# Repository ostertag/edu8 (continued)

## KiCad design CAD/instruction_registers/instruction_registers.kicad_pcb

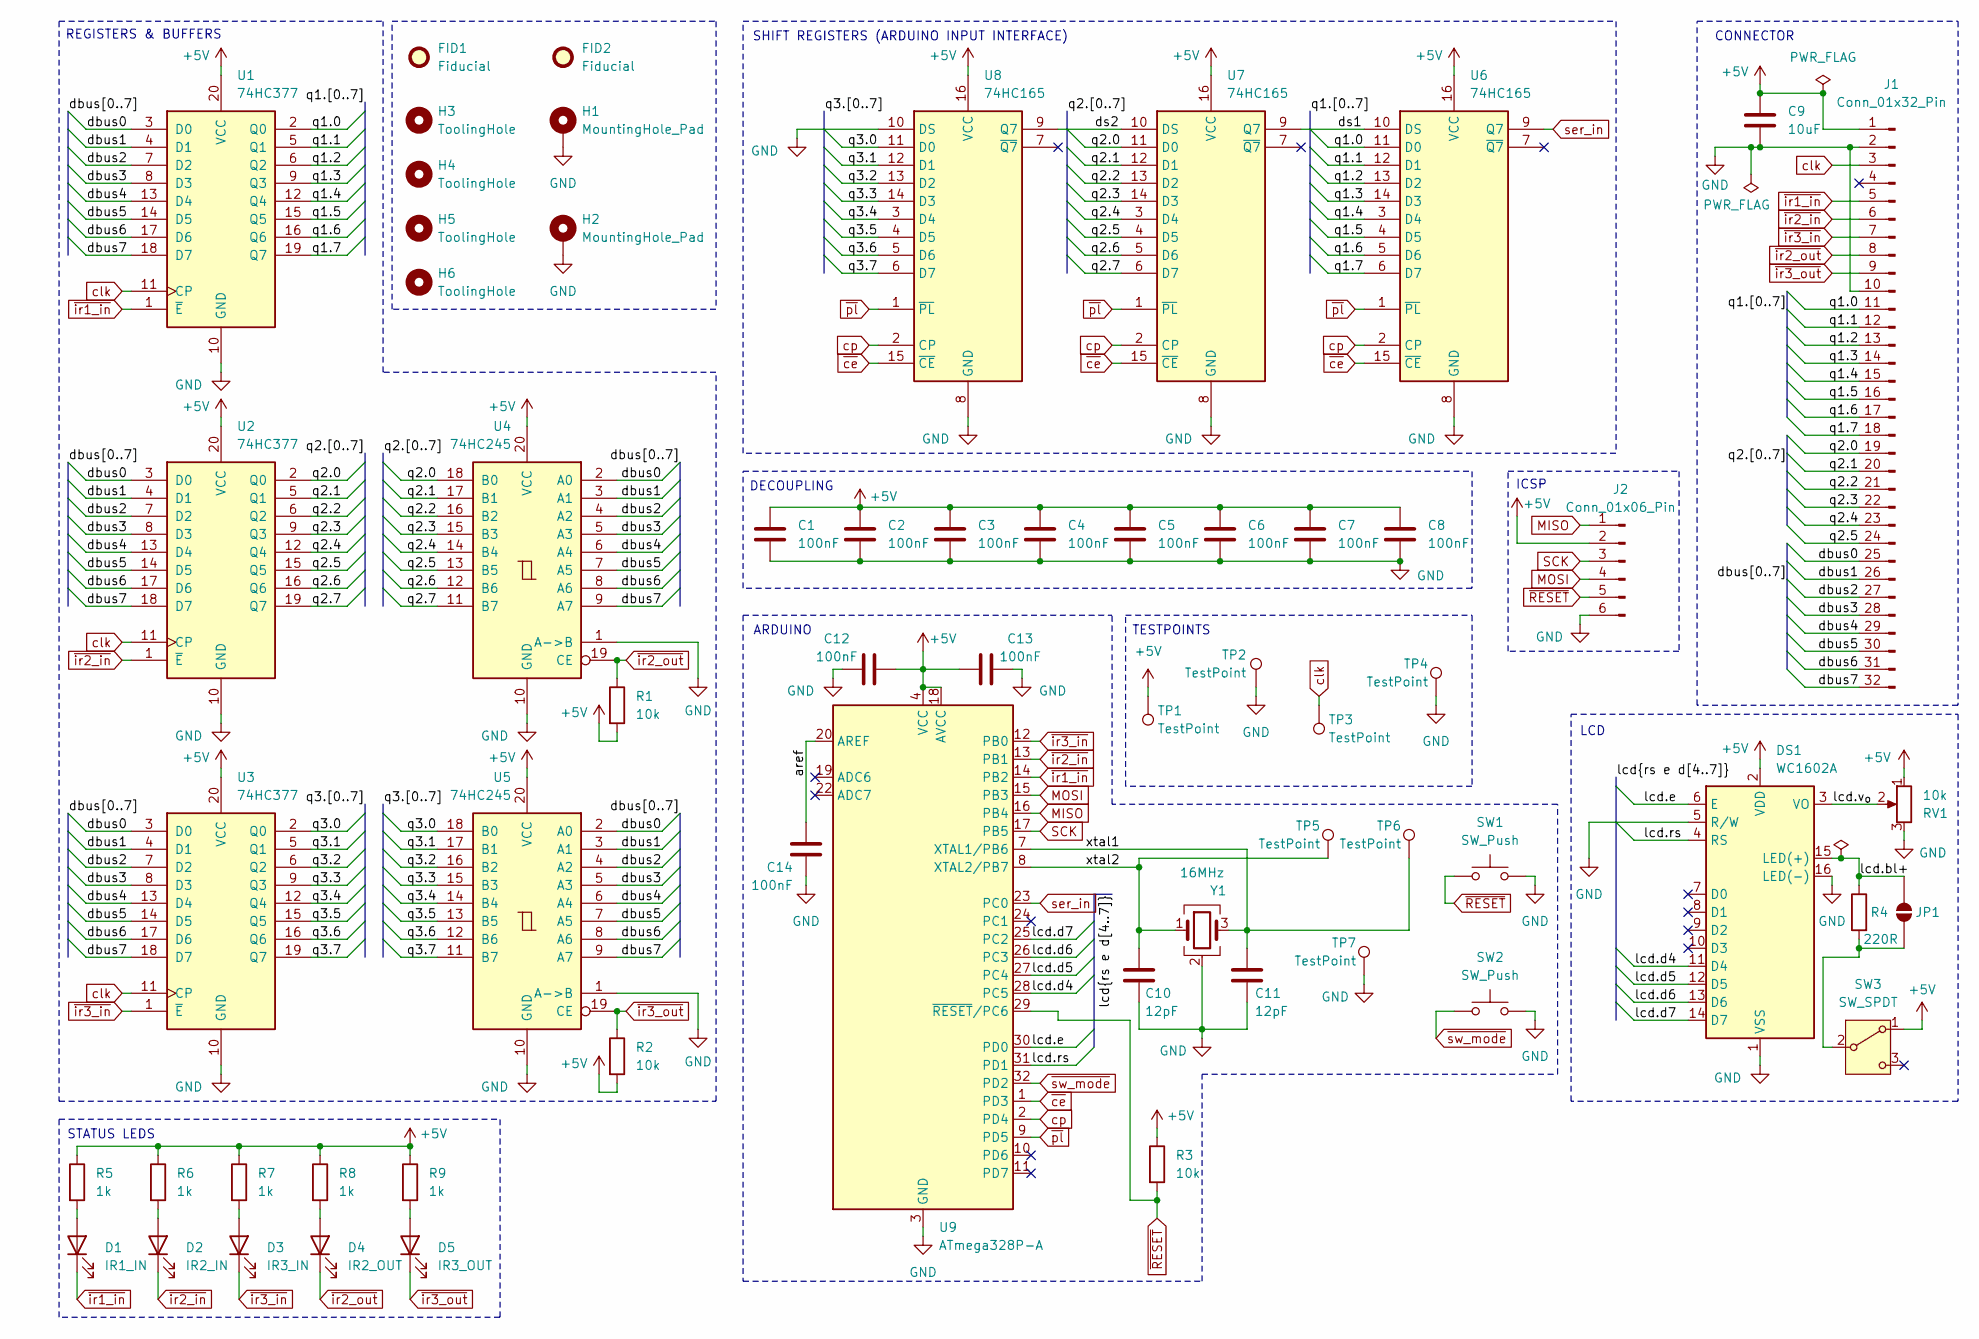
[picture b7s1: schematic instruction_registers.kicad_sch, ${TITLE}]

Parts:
C1, C2, C3, C4, C5, C6, C7, C8, C12, C13, C14: 100nF; C_0805_2012Metric; LCSC C28233
C9: 10uF; C_0805_2012Metric; LCSC C15850
C10, C11: 12pF; C_0805_2012Metric; LCSC C1792
D1: IR1_IN; LED_0805_2012Metric; LCSC C2297
D2: IR2_IN; LED_0805_2012Metric; LCSC C2297
D3: IR3_IN; LED_0805_2012Metric; LCSC C2297
D4: IR2_OUT; LED_0805_2012Metric; LCSC C2296
D5: IR3_OUT; LED_0805_2012Metric; LCSC C2296
DS1: WC1602A
FID1, FID2: Fiducial; Fiducial_0.5mm_Mask1mm
H1, H2: MountingHole_Pad; MountingHole_2.5mm_Pad_Via
H3, H4, H5, H6: ToolingHole; ToolingHole_1.152mm
J1: Conn_01x32_Pin; PinHeader_2x16_P2.54mm_Horizontal; LCSC C18905914
J2: Conn_01x06_Pin; PinHeader_2x03_P2.54mm_Vertical
JP1: SolderJumper_2_Open; SolderJumper-2_P1.3mm_Open_RoundedPad1.0x1.5mm
R1, R2, R3: 10k; R_0805_2012Metric; LCSC C17414
R4: 220R; R_0805_2012Metric; LCSC C17557
R5, R6, R7, R8, R9: 1k; R_0805_2012Metric; LCSC C17513
RV1: 10k; Potentiometer_Bourns_3314J_Vertical; LCSC C36376
SW1, SW2: SW_Push; SW_Push_1P1T_XKB_TS-1187A; LCSC C318884
SW3: SW_SPDT; SW_SPDT_PCM12; LCSC C221841
TP1, TP2, TP3, TP4, TP5, TP6, TP7: TestPoint; TestPoint_THTPad_D1.0mm_Drill0.5mm
U1, U2, U3: 74HC377; SO-20_5.3x12.6mm_P1.27mm; LCSC C7647
U4, U5: 74HC245; SOIC-20W_7.5x12.8mm_P1.27mm; LCSC C5625
U6, U7, U8: 74HC165; SO-16_3.9x9.9mm_P1.27mm; LCSC C5613
U9: ATmega328P-A; TQFP-32_7x7mm_P0.8mm; LCSC C14877
Y1: 16MHz; Crystal_SMD_3225-4Pin_3.2x2.5mm; LCSC C13738

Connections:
+5V: C1.1, C2.1, C3.1, C4.1, C5.1, C6.1, C7.1, C8.1, C9.1, C12.2, C13.1, DS1.2 (VDD), J1.1, J2.2, R1.2, R2.2, R3.1, R5.1, R6.1, R7.1, R8.1, R9.1, RV1.1, SW3.1 (A), TP1.1 (1_1), U1.20 (VCC), U2.20 (VCC), U3.20 (VCC), U4.20 (VCC), U5.20 (VCC), U6.16 (VCC), U7.16 (VCC), U8.16 (VCC), U9.4 (VCC), U9.6 (VCC), U9.18 (AVCC)
/aref: C14.1, U9.20 (AREF)
/dbus0: J1.25, U1.3 (D0), U2.3 (D0), U3.3 (D0), U4.2 (A0), U5.2 (A0)
/dbus1: J1.26, U1.4 (D1), U2.4 (D1), U3.4 (D1), U4.3 (A1), U5.3 (A1)
/dbus2: J1.27, U1.7 (D2), U2.7 (D2), U3.7 (D2), U4.4 (A2), U5.4 (A2)
/dbus3: J1.28, U1.8 (D3), U2.8 (D3), U3.8 (D3), U4.5 (A3), U5.5 (A3)
/dbus4: J1.29, U1.13 (D4), U2.13 (D4), U3.13 (D4), U4.6 (A4), U5.6 (A4)
/dbus5: J1.30, U1.14 (D5), U2.14 (D5), U3.14 (D5), U4.7 (A5), U5.7 (A5)
/dbus6: J1.31, U1.17 (D6), U2.17 (D6), U3.17 (D6), U4.8 (A6), U5.8 (A6)
/dbus7: J1.32, U1.18 (D7), U2.18 (D7), U3.18 (D7), U4.9 (A7), U5.9 (A7)
/ds1: U6.10 (DS), U7.9 (Q7)
/ds2: U7.10 (DS), U8.9 (Q7)
/lcd.bl+: DS1.15 (LED(+)), JP1.2 (B), R4.1
/lcd.d4: DS1.11 (D4), U9.28 (PC5)
/lcd.d5: DS1.12 (D5), U9.27 (PC4)
/lcd.d6: DS1.13 (D6), U9.26 (PC3)
/lcd.d7: DS1.14 (D7), U9.25 (PC2)
/lcd.e: DS1.6 (E), U9.30 (PD0)
/lcd.rs: DS1.4 (RS), U9.31 (PD1)
/lcd.v_{o}: DS1.3 (VO), RV1.2
/q1.0: J1.11, U1.2 (Q0), U6.11 (D0)
/q1.1: J1.12, U1.5 (Q1), U6.12 (D1)
/q1.2: J1.13, U1.6 (Q2), U6.13 (D2)
/q1.3: J1.14, U1.9 (Q3), U6.14 (D3)
/q1.4: J1.15, U1.12 (Q4), U6.3 (D4)
/q1.5: J1.16, U1.15 (Q5), U6.4 (D5)
/q1.6: J1.17, U1.16 (Q6), U6.5 (D6)
/q1.7: J1.18, U1.19 (Q7), U6.6 (D7)
/q2.0: J1.19, U2.2 (Q0), U4.18 (B0), U7.11 (D0)
/q2.1: J1.20, U2.5 (Q1), U4.17 (B1), U7.12 (D1)
/q2.2: J1.21, U2.6 (Q2), U4.16 (B2), U7.13 (D2)
/q2.3: J1.22, U2.9 (Q3), U4.15 (B3), U7.14 (D3)
/q2.4: J1.23, U2.12 (Q4), U4.14 (B4), U7.3 (D4)
/q2.5: J1.24, U2.15 (Q5), U4.13 (B5), U7.4 (D5)
/q2.6: U2.16 (Q6), U4.12 (B6), U7.5 (D6)
/q2.7: U2.19 (Q7), U4.11 (B7), U7.6 (D7)
/q3.0: U3.2 (Q0), U5.18 (B0), U8.11 (D0)
/q3.1: U3.5 (Q1), U5.17 (B1), U8.12 (D1)
/q3.2: U3.6 (Q2), U5.16 (B2), U8.13 (D2)
/q3.3: U3.9 (Q3), U5.15 (B3), U8.14 (D3)
/q3.4: U3.12 (Q4), U5.14 (B4), U8.3 (D4)
/q3.5: U3.15 (Q5), U5.13 (B5), U8.4 (D5)
/q3.6: U3.16 (Q6), U5.12 (B6), U8.5 (D6)
/q3.7: U3.19 (Q7), U5.11 (B7), U8.6 (D7)
/xtal1: C11.1, TP6.1 (1_1), U9.7 (XTAL1/PB6), Y1.3
/xtal2: C10.1, TP5.1 (1_1), U9.8 (XTAL2/PB7), Y1.1
GND: C1.2, C2.2, C3.2, C4.2, C5.2, C6.2, C7.2, C8.2, C9.2, C10.2, C11.2, C12.1, C13.2, C14.2, DS1.1 (VSS), DS1.5 (R/W), DS1.16 (LED(-)), H1.1 (1_1), H2.1 (1_1), J1.2, J1.10, J2.6, RV1.3, SW1.2, SW2.2, TP2.1 (1_1), TP4.1 (1_1), TP7.1 (1_1), U1.10 (GND), U2.10 (GND), U3.10 (GND), U4.1 (A->B), U4.10 (GND), U5.1 (A->B), U5.10 (GND), U6.8 (GND), U7.8 (GND), U8.8 (GND), U8.10 (DS), U9.3 (GND), U9.5 (GND), U9.21 (GND), Y1.2 (G), Y1.4 (G)
MISO: J2.1, U9.16 (PB4)
MOSI: J2.4, U9.15 (PB3)
unnamed: D1.2 (A), R5.2
unnamed: D2.2 (A), R6.2
unnamed: D3.2 (A), R7.2
unnamed: D4.2 (A), R8.2
unnamed: D5.2 (A), R9.2
unnamed: JP1.1 (A), R4.2, SW3.2 (B)
SCK: J2.3, U9.17 (PB5)
clk: J1.3, TP3.1 (1_1), U1.11 (CP), U2.11 (CP), U3.11 (CP)
cp: U6.2 (CP), U7.2 (CP), U8.2 (CP), U9.2 (PD4)
ser_in: U6.9 (Q7), U9.23 (PC0)
~RESET: J2.5, R3.2, SW1.1, U9.29 (~RESET/PC6)
~ce: U6.15 (~CE), U7.15 (~CE), U8.15 (~CE), U9.1 (PD3)
~ir1_in: D1.1 (K), J1.5, U1.1 (~E), U9.14 (PB2)
~ir2_in: D2.1 (K), J1.6, U2.1 (~E), U9.13 (PB1)
~ir2_out: D4.1 (K), J1.8, R1.1, U4.19 (CE)
~ir3_in: D3.1 (K), J1.7, U3.1 (~E), U9.12 (PB0)
~ir3_out: D5.1 (K), J1.9, R2.1, U5.19 (CE)
~pl: U6.1 (~PL), U7.1 (~PL), U8.1 (~PL), U9.9 (PD5)
~sw_mode: SW2.1, U9.32 (PD2)

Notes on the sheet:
ARDUINO
TESTPOINTS
CONNECTOR
STATUS LEDS
DECOUPLING
LCD
ICSP
REGISTERS & BUFFERS
SHIFT REGISTERS (ARDUINO INPUT INTERFACE)

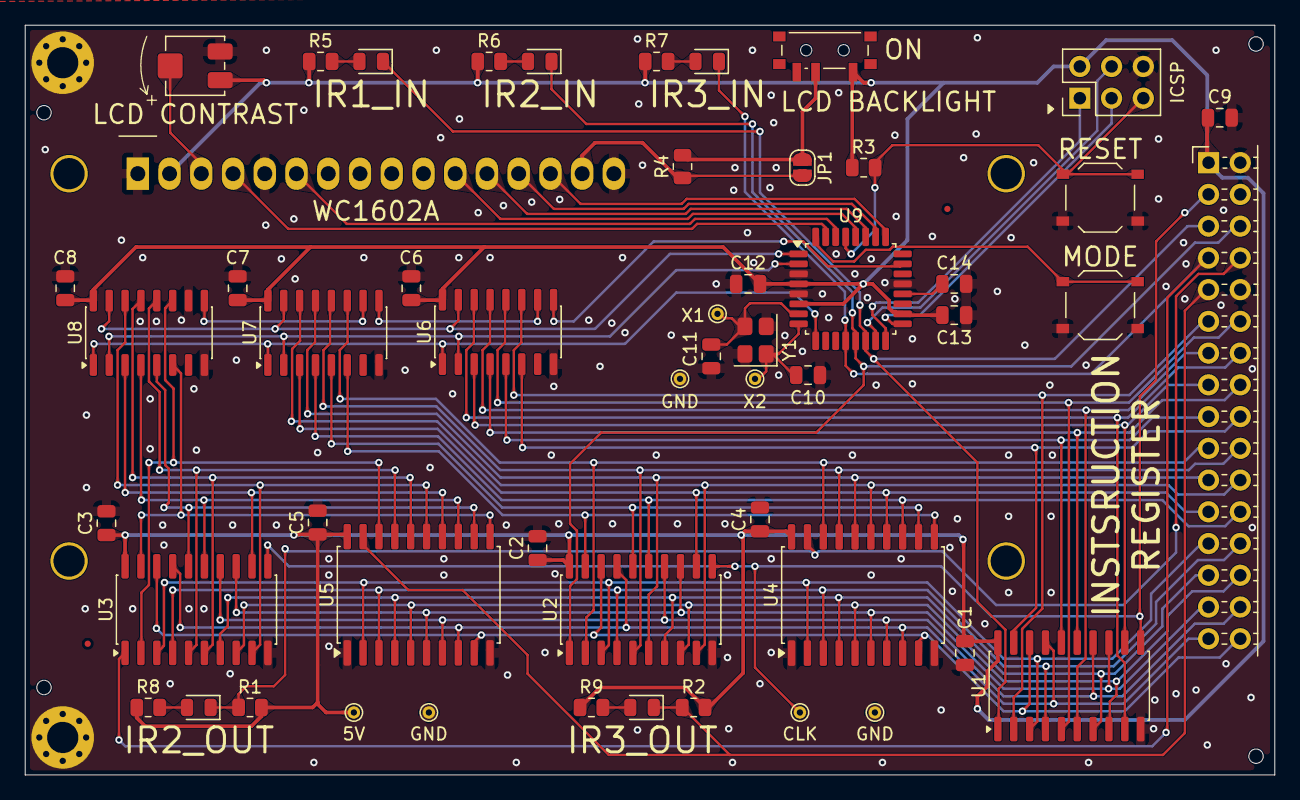
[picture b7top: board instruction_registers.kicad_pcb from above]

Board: 2 copper layers, 100.0 x 60.0 mm, 62 parts (1 on the bottom side), 68 nets.

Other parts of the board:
Ref**: Val**; by-nc-sa.eu

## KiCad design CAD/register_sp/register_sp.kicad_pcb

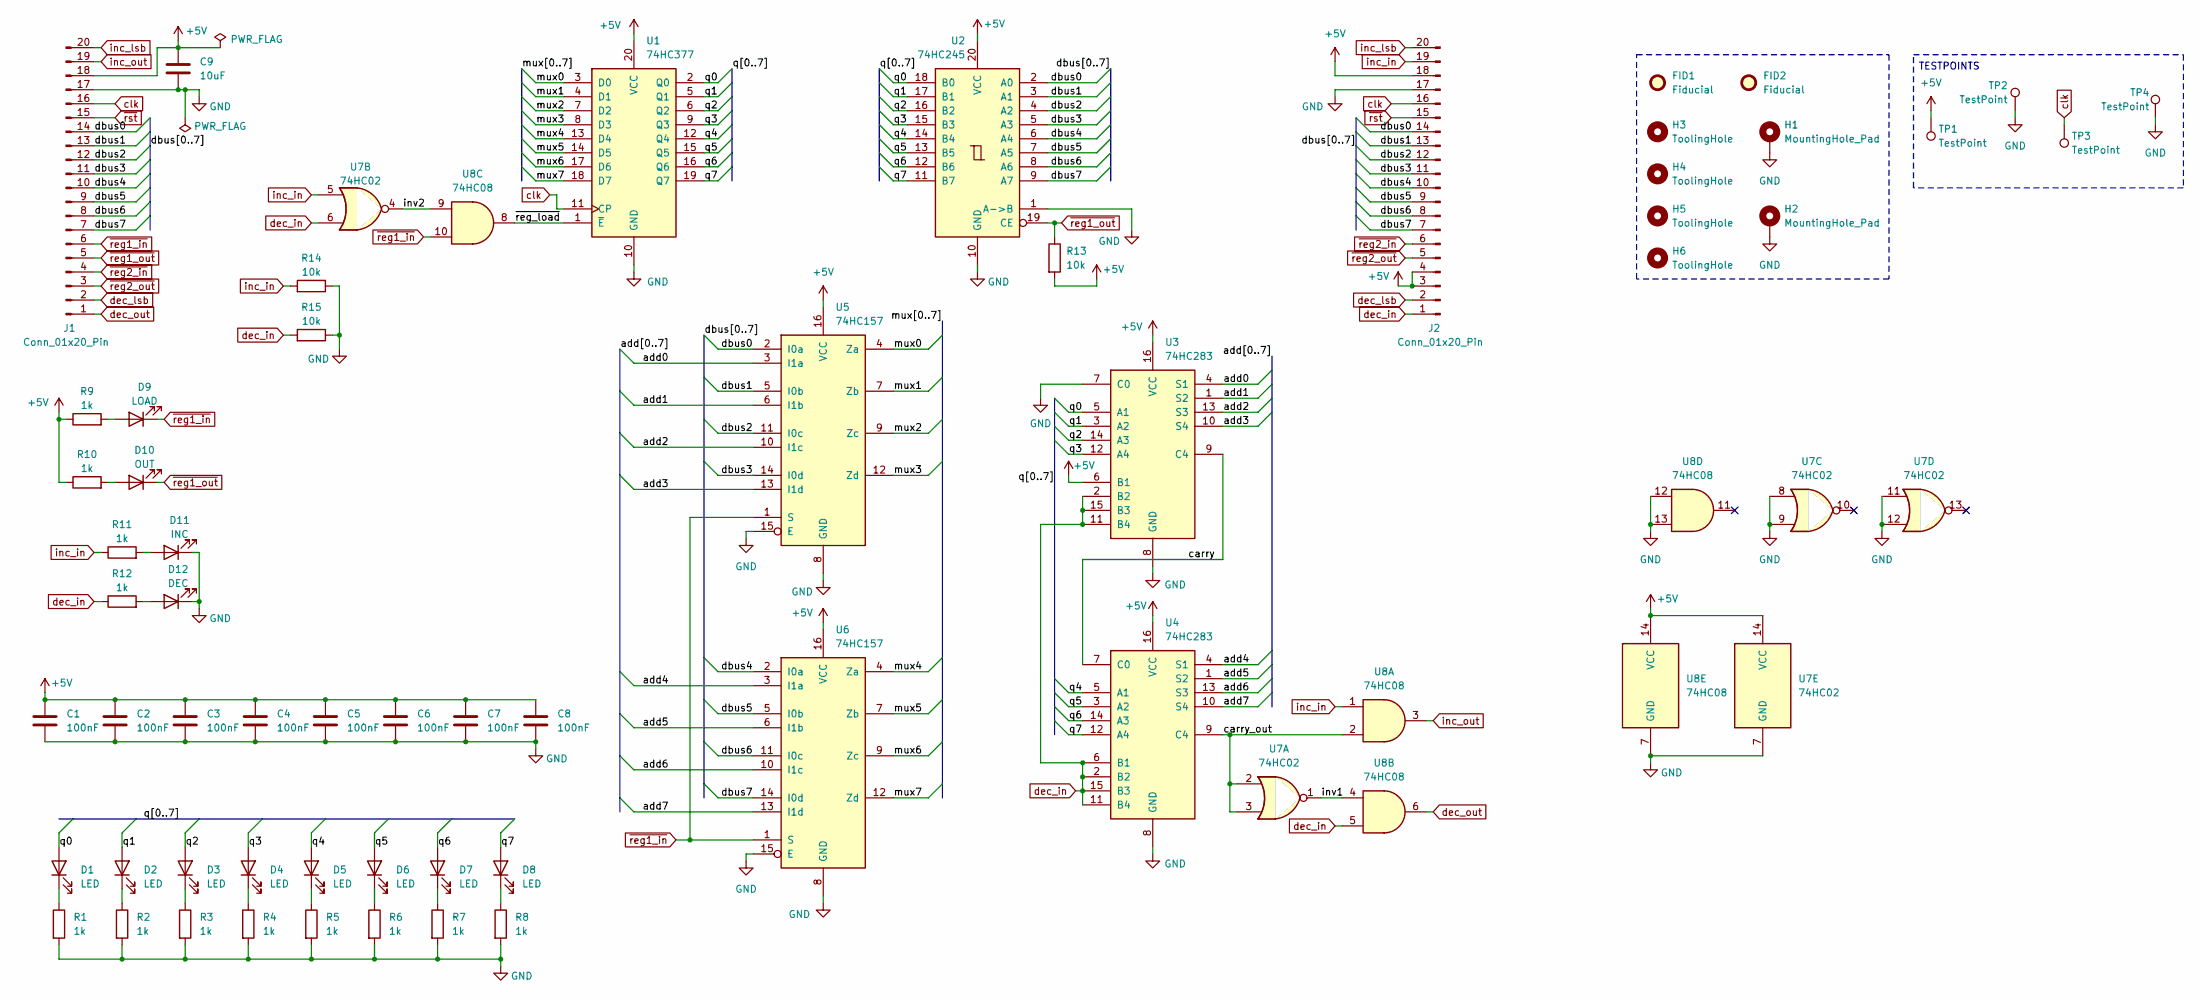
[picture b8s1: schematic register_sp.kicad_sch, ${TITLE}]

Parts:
C1, C2, C3, C4, C5, C6, C7, C8: 100nF; C_0805_2012Metric; LCSC C28233
C9: 10uF; C_0805_2012Metric; LCSC C15850
D1, D2, D3, D4, D5, D6, D7, D8: LED; LED_0805_2012Metric; LCSC C84256
D9: LOAD; LED_0805_2012Metric; LCSC C2297
D10: OUT; LED_0805_2012Metric; LCSC C2296
D11: INC; LED_0805_2012Metric
D12: DEC; LED_0805_2012Metric
FID1, FID2: Fiducial; Fiducial_0.5mm_Mask1mm
H1, H2: MountingHole_Pad; MountingHole_2.5mm_Pad_Via
H3, H4, H5, H6: ToolingHole; ToolingHole_1.152mm
J1: Conn_01x20_Pin; PinHeader_2x10_P2.54mm_Horizontal; LCSC C18905907
J2: Conn_01x20_Pin; PinSocket_2x10_P2.54mm_Horizontal; LCSC C2897429
R1, R2, R3, R4, R5, R6, R7, R8, R9, R10, R11, R12: 1k; R_0805_2012Metric; LCSC C17513
R13, R14, R15: 10k; R_0805_2012Metric; LCSC C17414
TP1, TP2, TP3, TP4: TestPoint; TestPoint_THTPad_D1.0mm_Drill0.5mm
U1: 74HC377; SO-20_5.3x12.6mm_P1.27mm; LCSC C7647
U2: 74HC245; SOIC-20W_7.5x12.8mm_P1.27mm; LCSC C5625
U3, U4: 74HC283; SO-16_3.9x9.9mm_P1.27mm; LCSC C24833609
U5, U6: 74HC157; SO-16_3.9x9.9mm_P1.27mm; LCSC C6823
U7: 74HC02; SO-14_3.9x8.65mm_P1.27mm; LCSC C350559
U8: 74HC08; SO-14_3.9x8.65mm_P1.27mm; LCSC C5593

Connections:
+5V: C1.1, C2.1, C3.1, C4.1, C5.1, C6.1, C7.1, C8.1, C9.1, J1.18, J2.3, J2.4, J2.18, R9.1, R10.1, R13.2, TP1.1 (1_1), U1.20 (VCC), U2.20 (VCC), U3.6 (B1), U3.16 (VCC), U4.16 (VCC), U5.16 (VCC), U6.16 (VCC), U7.14 (VCC), U8.14 (VCC)
/add0: U3.4 (S1), U5.3 (I1a)
/add1: U3.1 (S2), U5.6 (I1b)
/add2: U3.13 (S3), U5.10 (I1c)
/add3: U3.10 (S4), U5.13 (I1d)
/add4: U4.4 (S1), U6.3 (I1a)
/add5: U4.1 (S2), U6.6 (I1b)
/add6: U4.13 (S3), U6.10 (I1c)
/add7: U4.10 (S4), U6.13 (I1d)
/carry: U3.9 (C4), U4.7 (C0)
/carry_out: U4.9 (C4), U7.2, U7.3, U8.2
/dbus0: J1.14, J2.14, U2.2 (A0), U5.2 (I0a)
/dbus1: J1.13, J2.13, U2.3 (A1), U5.5 (I0b)
/dbus2: J1.12, J2.12, U2.4 (A2), U5.11 (I0c)
/dbus3: J1.11, J2.11, U2.5 (A3), U5.14 (I0d)
/dbus4: J1.10, J2.10, U2.6 (A4), U6.2 (I0a)
/dbus5: J1.9, J2.9, U2.7 (A5), U6.5 (I0b)
/dbus6: J1.8, J2.8, U2.8 (A6), U6.11 (I0c)
/dbus7: J1.7, J2.7, U2.9 (A7), U6.14 (I0d)
/inv1: U7.1, U8.4
/inv2: U7.4, U8.9
/mux0: U1.3 (D0), U5.4 (Za)
/mux1: U1.4 (D1), U5.7 (Zb)
/mux2: U1.7 (D2), U5.9 (Zc)
/mux3: U1.8 (D3), U5.12 (Zd)
/mux4: U1.13 (D4), U6.4 (Za)
/mux5: U1.14 (D5), U6.7 (Zb)
/mux6: U1.17 (D6), U6.9 (Zc)
/mux7: U1.18 (D7), U6.12 (Zd)
/q0: D1.2 (A), U1.2 (Q0), U2.18 (B0), U3.5 (A1)
/q1: D2.2 (A), U1.5 (Q1), U2.17 (B1), U3.3 (A2)
/q2: D3.2 (A), U1.6 (Q2), U2.16 (B2), U3.14 (A3)
/q3: D4.2 (A), U1.9 (Q3), U2.15 (B3), U3.12 (A4)
/q4: D5.2 (A), U1.12 (Q4), U2.14 (B4), U4.5 (A1)
/q5: D6.2 (A), U1.15 (Q5), U2.13 (B5), U4.3 (A2)
/q6: D7.2 (A), U1.16 (Q6), U2.12 (B6), U4.14 (A3)
/q7: D8.2 (A), U1.19 (Q7), U2.11 (B7), U4.12 (A4)
/~reg_load: U1.1 (~E), U8.8
GND: C1.2, C2.2, C3.2, C4.2, C5.2, C6.2, C7.2, C8.2, C9.2, D11.1 (K), D12.1 (K), H1.1 (1_1), H2.1 (1_1), J1.17, J2.17, R1.2, R2.2, R3.2, R4.2, R5.2, R6.2, R7.2, R8.2, R14.1, R15.1, TP2.1 (1_1), TP4.1 (1_1), U1.10 (GND), U2.1 (A->B), U2.10 (GND), U3.7 (C0), U3.8 (GND), U4.8 (GND), U5.8 (GND), U5.15 (E), U6.8 (GND), U6.15 (E), U7.7 (GND), U7.8, U7.9, U7.11, U7.12, U8.7 (GND), U8.12, U8.13
unnamed: D1.1 (K), R1.1
unnamed: D2.1 (K), R2.1
unnamed: D3.1 (K), R3.1
unnamed: D4.1 (K), R4.1
unnamed: D5.1 (K), R5.1
unnamed: D6.1 (K), R6.1
unnamed: D7.1 (K), R7.1
unnamed: D8.1 (K), R8.1
unnamed: D9.2 (A), R9.2
unnamed: D10.2 (A), R10.2
unnamed: D11.2 (A), R11.2
unnamed: D12.2 (A), R12.2
clk: J1.16, J2.16, TP3.1 (1_1), U1.11 (CP)
dec_in: J2.1, R12.1, R15.2, U3.2 (B2), U3.11 (B4), U3.15 (B3), U4.2 (B2), U4.6 (B1), U4.11 (B4), U4.15 (B3), U7.6, U8.5
dec_lsb: J1.2, J2.2
dec_out: J1.1, U8.6
inc_in: J2.19, R11.1, R14.2, U7.5, U8.1
inc_lsb: J1.20, J2.20
inc_out: J1.19, U8.3
~reg1_in: D9.1 (K), J1.6, U5.1 (S), U6.1 (S), U8.10
~reg1_out: D10.1 (K), J1.5, R13.1, U2.19 (CE)
~reg2_in: J1.4, J2.6
~reg2_out: J1.3, J2.5
~rst: J1.15, J2.15

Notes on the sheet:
TESTPOINTS

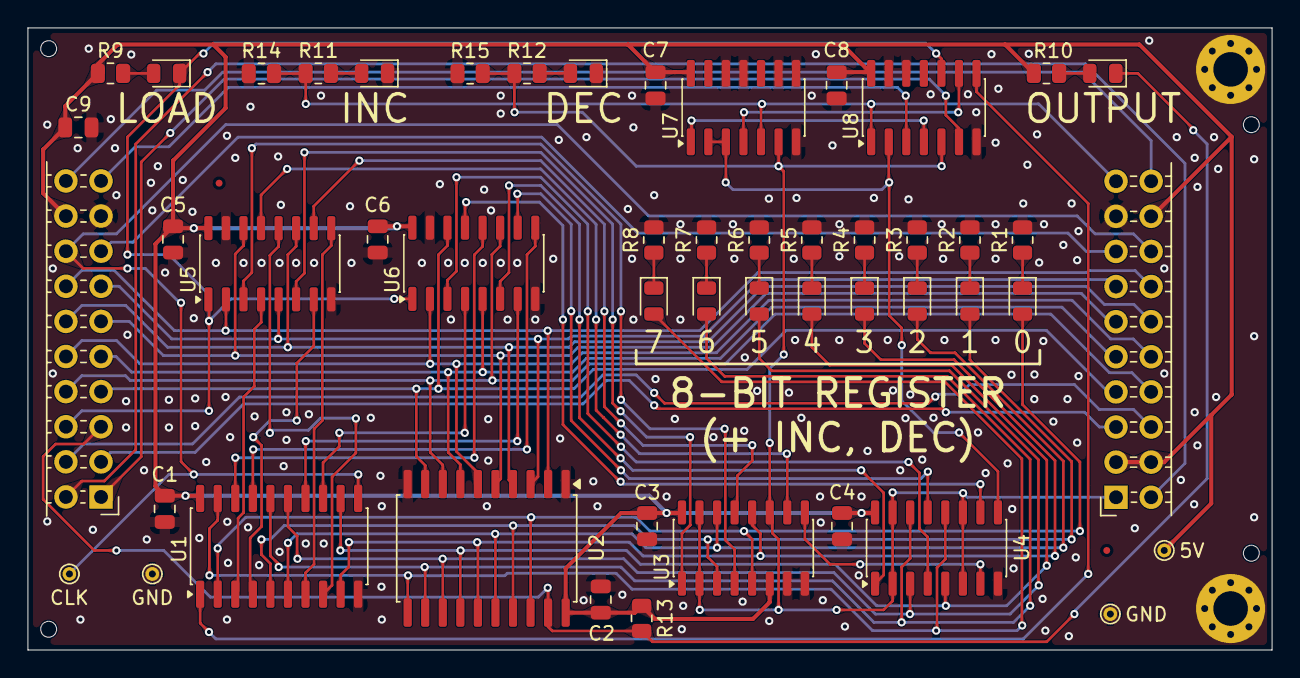
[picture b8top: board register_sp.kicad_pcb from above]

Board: 2 copper layers, 90.0 x 45.0 mm, 59 parts (1 on the bottom side), 63 nets.

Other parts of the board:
Ref**: Val**; by-nc-sa.eu

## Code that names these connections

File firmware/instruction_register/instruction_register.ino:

#include <LiquidCrystal.h>

// shift registers
const int CP_PIN = 4;
const int DATA_IN_PIN = 14;
const int CE_PIN = 3;
const int PL_PIN = 5;

// control signals
const int IR1_IN_PIN = 10;
const int IR2_IN_PIN = 9;
const int IR3_IN_PIN = 8;

// button
const int SW_MODE_PIN = 2;

// lcd
const int RS_PIN = 1;
const int E_PIN = 0;
const int D4_PIN = 19;
const int D5_PIN = 18;
const int D6_PIN = 17;
const int D7_PIN = 16;

LiquidCrystal lcd(RS_PIN, E_PIN, D4_PIN, D5_PIN, D6_PIN, D7_PIN);

bool ir1_in_state, ir2_in_state, ir3_in_state;

void loadWord() {
    digitalWrite(PL_PIN, LOW);
    delay(1);
    digitalWrite(PL_PIN, HIGH);
    delay(1);
}

uint8_t readByte() {
    uint8_t val = 0;
    for (int i = 7; i >= 0; i--) {
        val |= (digitalRead(DATA_IN_PIN) << i);
        digitalWrite(CP_PIN, HIGH);
        delay(1);
        digitalWrite(CP_PIN, LOW);
        delay(1);
    }
    return val;
}

void setup() {

  // shift registers
  pinMode(CP_PIN, OUTPUT);
  digitalWrite(CP_PIN, LOW);
  pinMode(CE_PIN, OUTPUT);
  digitalWrite(CE_PIN, LOW);
  pinMode(PL_PIN, OUTPUT);
  digitalWrite(PL_PIN, HIGH);
  pinMode(DATA_IN_PIN, INPUT);

  // control signals
  pinMode(IR1_IN_PIN, INPUT);
  pinMode(IR2_IN_PIN, INPUT);
  pinMode(IR3_IN_PIN, INPUT);
  
  // button TMP
  pinMode(SW_MODE_PIN, INPUT_PULLUP);

  // lcd
  lcd.begin(16, 2);
  lcd.clear();

  ir1_in_state = false;
  ir2_in_state = false;
  ir3_in_state = false;
  
}

char hexChar(uint8_t nibble) {
  if (nibble <= 9) return '0' + nibble;
  return 'A' + nibble - 10;
}

void updateDisplay() {
  loadWord();
  uint8_t q1 = readByte();
  uint8_t q2 = readByte();
  uint8_t q3 = readByte();
  lcd.clear();
  lcd.print(hexChar((q1 >> 4) & 0x0f));
  lcd.print(hexChar(q1 & 0x0f));
  lcd.print("  ");
  lcd.print(hexChar((q2 >> 4) & 0x0f));
  lcd.print(hexChar(q2 & 0x0f));
  lcd.print("  ");
  lcd.print(hexChar((q3 >> 4) & 0x0f));
  lcd.print(hexChar(q3 & 0x0f));
}

void loop() {
  // bool change = false;
  // if (digitalRead(IR1_IN_PIN) != ir1_in_state) {
  //   ir1_in_state = !ir1_in_state;
  //   change = true;
  // }
  // if (digitalRead(IR2_IN_PIN) != ir2_in_state) {
  //   ir2_in_state = !ir2_in_state;
  //   change = true;
  // }
  // if (digitalRead(IR3_IN_PIN) != ir3_in_state) {
  //   ir3_in_state = !ir3_in_state;
  //   change = true;
  // }

  // if (change) {
  //   updateDisplay();
  // }

  // delay(10);

  static int counter = 0;
  lcd.clear();
  lcd.print("Hello, World!");
  lcd.setCursor(0, 1);
  lcd.print("counter: ");
  lcd.print(counter++);
  delay(2000);
}

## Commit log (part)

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2026-02-26 Add vias, GND planes, QR code, version and other details
2026-02-26 Other changes
2026-03-01 setup directories
2026-03-01 add general register
2026-03-01 add NetClasses, TestPads, remove jumper pins
2026-03-03 fix HC245 dir signal
2026-03-03 add components to library
2026-03-03 add text variables for revision, etc.
2026-03-03 fix variables
2026-03-03 add Motherboard, schematic not finished
2026-03-03 add Status Word schematic
2026-03-04 add Status Word PCB, not finished
2026-03-09 add mounting holes, pull-up, test points in SW
2026-03-10 update silkscreen qr code, license, add images
2026-03-10 add pull-up resistor to general register
2026-03-11 add tooling holes to SW, update libraries
2026-03-11 layout changes, adding mounting holes, modifying tooling holes and adding fiducials
2026-03-12 change buffer footprint in SW
2026-03-12 CLK test point, CC-BY-NC-SA
2026-03-16 update SW, add footprints and 3D models to library
2026-03-16 add Instruction Registers
2026-03-16 add Program Counter
2026-03-18 update General Register, add mounting holes, testpoints, LCSC numbers
2026-03-18 update SW, fix component rotations
2026-03-18 update IR, move crystal, change capacitors, add testpoints, ground planes
2026-03-18 update PC, move crystal, change capacitors, add testpoints
2026-03-19 update general register layout
2026-03-19 update teardrops in general register
2026-03-19 layout changes
2026-03-19 IR layout changes
2026-03-19 PC layout changes
2026-03-20 layout improvements for program counter
2026-03-21 general register layout changes
2026-03-21 SW layout changes
2026-03-21 PC centrovanie revision
2026-03-21 IR center revision
2026-03-22 SW add keystone 5015 testpoint, small layout improvements
2026-03-22 add slotted test point for 5V to general register
2026-03-22 rotation of RH5015 test point, small layout improvements
2026-03-22 add Step Counter
2026-03-22 update Step Counter, more ground planes
2026-03-22 step counter - layout improvements
2026-03-23 add SP register
2026-03-24 add SP layout without routing
2026-03-24 add SP PCB
2026-03-24 SP layout improvements
2026-03-27 update SP - change board order
2026-03-28 update SP label
2026-03-29 SP label improvements
2026-03-30 exclude known warnings in ERC and DRC
